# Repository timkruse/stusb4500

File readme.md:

# USB Type C Evaluation Board based on STUSB4500 by STM

This project implements the USB Type C connector based on the STM's STUSB4500 USB Power Delevery controller.
All signals are either routed to the dedicated USB connector or to an exteral connector to access signals such as I2C which is the config interface of the STUSB4500.  
The power lines are controled by FETs to suit the 100W specification of USB-C.

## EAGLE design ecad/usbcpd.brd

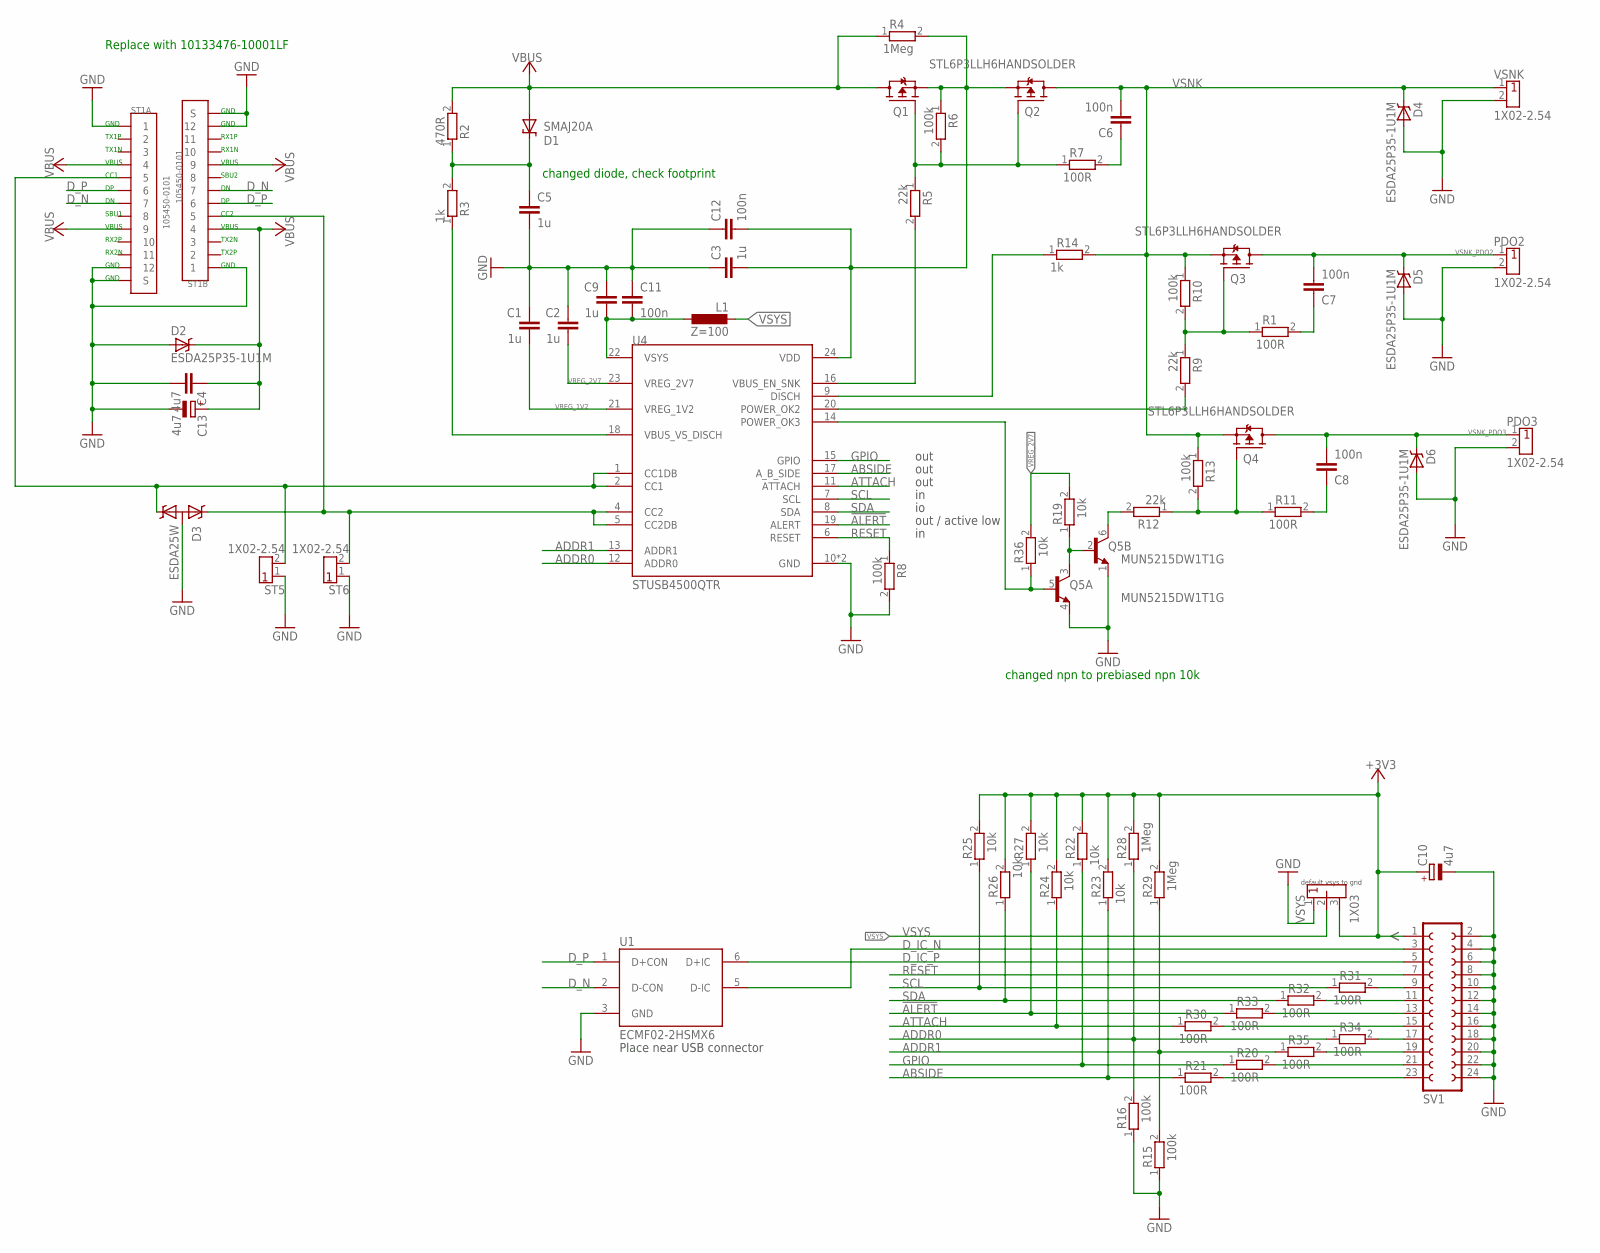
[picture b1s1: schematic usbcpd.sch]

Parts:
C1, C2, C3, C5, C9: 1u; 0805
C4: 4u7; 0805
C6, C7, C8, C11, C12: 100n; 0805
C10, C13: 4u7; E2-5
D1: SMAJ20A; SMBJ; MPN SMAJ20A
D2, D4, D5, D6: ESDA25P35-1U1M; QFN1610
D3: ESDA25W; SOT323-3
L1: Z=100; 0805; MPN MPZ2012S101AT000
PDO2, PDO3: 1X02-2.54
Q1, Q2, Q3, Q4: STL6P3LLH6HANDSOLDER; POWERFLAT-TYPEC-HANDSOLDER
Q5: MUN5215DW1T1G; SOT363; MPN MUN5215DW1T1G
R1, R7, R11, R20, R21, R30, R31, R32, R33, R34, R35: 100R; 0805
R2: 470R; 0805
R3, R14: 1k; 0805
R4, R28, R29: 1Meg; 0805
R5, R9, R12: 22k; 0805
R6, R8, R10, R13, R15, R16: 100k; 0805
R19, R22, R23, R24, R25, R26, R27, R36: 10k; 0805
ST1: 105450-0101
ST5, ST6: 1X02-2.54
SV1: FE12-2
U1: ECMF02-2HSMX6; UQFN6
U4: STUSB4500QTR; QFN24EP
VSNK: 1X02-2.54
VSYS: 1X03; 1X03-2.54

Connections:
!ALERT: R27.1, R33.1, U4.19 (ALERT)
+3V3: C10.+, R22.2, R23.2, R24.2, R25.2, R26.2, R27.2, R28.2, R29.2, SV1.1, VSYS.3
ABSIDE: R21.1, R23.1, U4.17 (A_B_SIDE)
ADDR0: R16.2, R28.1, R34.1, U4.12 (ADDR0)
ADDR1: R15.2, R29.1, R35.1, U4.13 (ADDR1)
ATTACH: R24.1, R30.1, U4.11 (ATTACH)
CC1: D3.2 (C2), ST1.A5 (5), ST5.2, U4.1 (CC1DB), U4.2 (CC1)
CC2: D3.1 (C1), ST1.B5 (5), ST6.2, U4.4 (CC2), U4.5 (CC2DB)
DISCH: R14.1, U4.9 (DISCH)
D_IC_N: SV1.3, U1.5 (D-IC)
D_IC_P: SV1.5, U1.6 (D+IC)
D_N: ST1.A7 (7), ST1.B7 (7), U1.2 (D-CON)
D_P: ST1.A6 (6), ST1.B6 (6), U1.1 (D+CON)
GND: C1.1, C2.1, C3.1, C4.2, C5.2, C9.1, C10.-, C11.1, C12.1, C13.-, D2.2 (A), D3.3 (A), D4.2 (A), D5.2 (A), D6.2 (A), PDO2.2, PDO3.2, Q5.1 (E), Q5.4 (E), R8.2, R15.1, R16.1, ST1.A1 (1), ST1.A12 (12), ST1.B1 (1), ST1.B12 (12), ST1.G1 (S), ST1.G2 (S), ST1.G3 (S), ST1.G4 (S), ST1.G5 (S), ST1.G6 (S), ST1.G7 (S), ST1.G8 (S), ST1.G9 (S), ST1.G10 (S), ST1.G11 (S), ST1.G12 (S), ST1.G13 (S), ST1.G14 (S), ST1.G15 (S), ST1.G16 (S), ST1.G17 (S), ST1.G18 (S), ST1.G19 (S), ST1.G20 (S), ST1.G21 (S), ST1.G22 (S), ST1.G23 (S), ST1.G24 (S), ST1.G25 (S), ST1.G26 (S), ST1.G27 (S), ST1.G28 (S), ST1.G29 (S), ST1.G30 (S), ST1.G31 (S), ST1.G32 (S), ST1.G33 (S), ST5.1, ST6.1, SV1.2, SV1.4, SV1.6, SV1.8, SV1.10, SV1.12, SV1.14, SV1.16, SV1.18, SV1.20, SV1.22, SV1.24, U1.3 (GND), U4.10 (GND), U4.TP (GND), VSNK.2, VSYS.1
GPIO: R20.1, R22.1, U4.15 (GPIO)
unnamed: C5.1, D1.C, R2.1, R3.2
unnamed: Q1.4 (G), Q2.4 (G), R5.1, R6.2, R7.1
unnamed: C6.1, R7.2
unnamed: C7.1, R1.2
unnamed: Q3.4 (G), R1.1, R9.1, R10.2
unnamed: C8.1, R11.2
unnamed: Q4.4 (G), R11.1, R12.1, R13.2
unnamed: R20.2, SV1.21
unnamed: R21.2, SV1.23
unnamed: R31.2, SV1.9
unnamed: R30.2, SV1.15
unnamed: R33.2, SV1.13
unnamed: R32.2, SV1.11
unnamed: R34.2, SV1.17
unnamed: R35.2, SV1.19
unnamed: C9.2, C11.2, L1.1, U4.22 (VSYS)
unnamed: Q5.2 (B), Q5.3 (C), R19.1
unnamed: Q5.6 (C), R12.2
PDO2: R9.2, U4.20 (POWER_OK2)
PDO3: Q5.5 (B), R36.1, U4.14 (POWER_OK3)
RESET: R8.1, SV1.7, U4.6 (RESET)
SCL: R25.1, R31.1, U4.7 (SCL)
SDA: R26.1, R32.1, U4.8 (SDA)
VBUS: C4.1, C13.+, D1.A, D2.1 (C), Q1.5 (D), R2.2, R4.1, ST1.A4 (4), ST1.A9 (9), ST1.B4 (4), ST1.B9 (9)
VBUS_EN_SNK: R5.2, U4.16 (VBUS_EN_SNK)
VBUS_VS_DISCH: R3.1, U4.18 (VBUS_VS_DISCH)
VDD: C3.2, C12.2, Q1.1 (S), Q1.2 (S), Q1.3 (S), Q2.1 (S), Q2.2 (S), Q2.3 (S), R4.2, R6.1, U4.24 (VDD)
VREG_1V2: C1.2, U4.21 (VREG_1V2)
VREG_2V7: C2.2, R19.2, R36.2, U4.23 (VREG_2V7)
VSNK: C6.2, D4.1 (C), Q2.5 (D), Q3.1 (S), Q3.2 (S), Q3.3 (S), Q4.1 (S), Q4.2 (S), Q4.3 (S), R10.1, R13.1, R14.2, VSNK.1
VSNK_PDO2: C7.2, D5.1 (C), PDO2.1, Q3.5 (D)
VSNK_PDO3: C8.2, D6.1 (C), PDO3.1, Q4.5 (D)
VSYS: L1.2, VSYS.2

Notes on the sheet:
GND
TX1P
TX1N
VBUS
CC1
CC2
SBU1
RX2P
RX2N
TX2N
TX2P
SBU2
RX1N
RX1P
Place near USB connector
out
out / active low
default vsys to gnd
changed npn to prebiased npn 10k
changed diode, check footprint
Replace with 10133476-10001LF

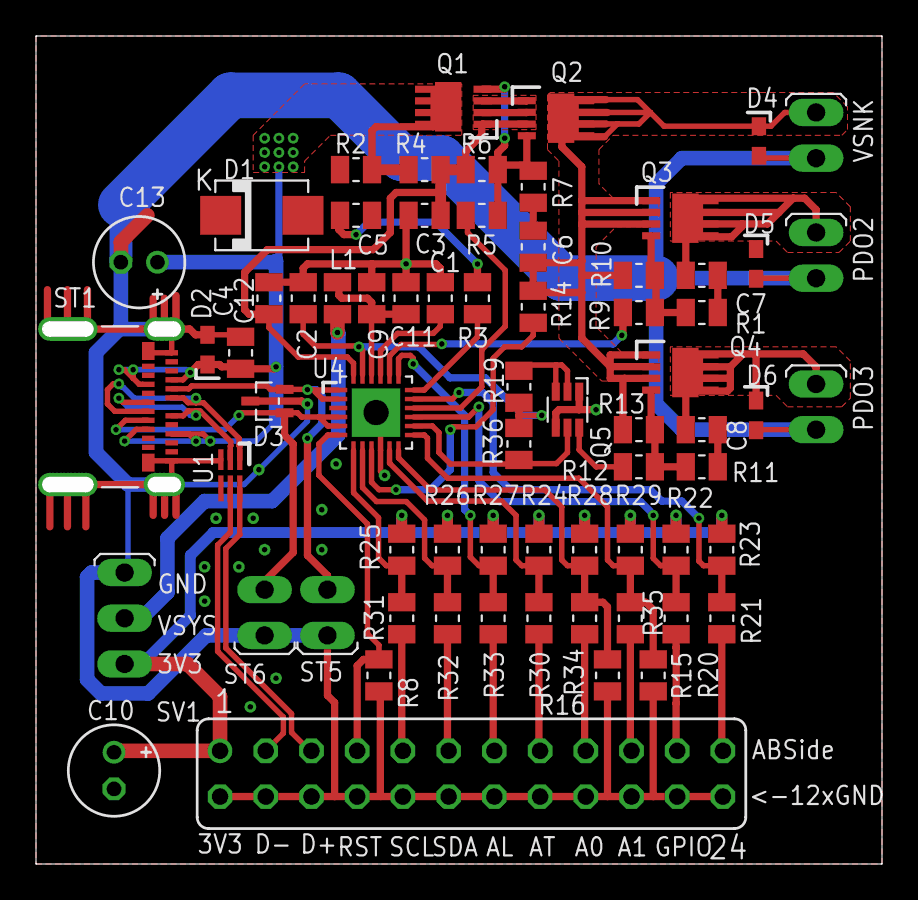
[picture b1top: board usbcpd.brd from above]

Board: 2 copper layers, 46.2 x 45.2 mm, 69 parts (0 on the bottom side), 48 nets.

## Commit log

2019-03-16 documentational improvements
2019-03-16 NVM Bits desciption improved
